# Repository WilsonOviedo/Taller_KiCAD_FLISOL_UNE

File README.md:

# Taller_KiCAD_FLISOL_UNE
Repositorio de taller de KiCAD realizado en el FLISOL 27/04/2019

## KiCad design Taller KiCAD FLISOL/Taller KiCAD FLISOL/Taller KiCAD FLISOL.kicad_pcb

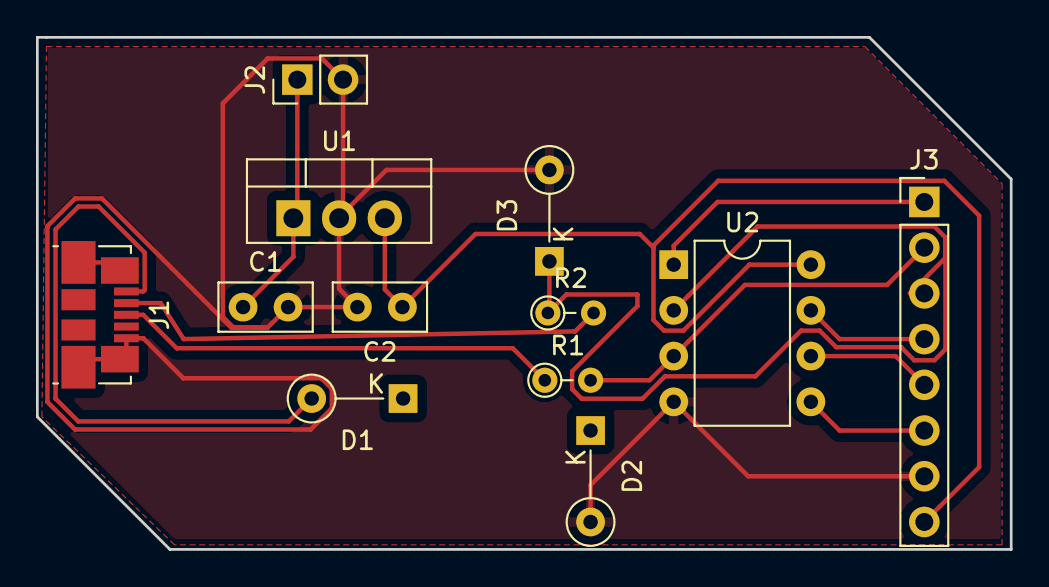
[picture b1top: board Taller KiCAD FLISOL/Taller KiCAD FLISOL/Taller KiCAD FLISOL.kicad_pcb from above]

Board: 2 copper layers, 54.1 x 28.4 mm, 12 parts (0 on the bottom side), 12 nets.

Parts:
C1: 0.33uF; C_Disc_D5.0mm_W2.5mm_P2.50mm
C2: 0.1uF; C_Disc_D5.0mm_W2.5mm_P2.50mm
D1: D; D_DO-35_SOD27_P5.08mm_Vertical_KathodeUp
D2, D3: D_Zener; D_DO-35_SOD27_P5.08mm_Vertical_KathodeUp
J1: USB_B_Micro; USB_Micro-B_Molex_47346-0001
J2: Conn_01x02_Male; PinHeader_1x02_P2.54mm_Vertical
J3: Conn_01x08_Male; PinHeader_1x08_P2.54mm_Vertical
R1, R2: 66.5ohms; R_Axial_DIN0204_L3.6mm_D1.6mm_P2.54mm_Vertical
U1: LM7805_TO220; TO-220-3_Vertical
U2: ATTINY85-20PU; DIP-8_W7.62mm

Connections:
+5V: D1.2, J1.1
/5V_Reg: C2.1, D1.1, J3.8, U1.3, U2.8
D+: D2.1, J3.2, R1.2, U2.3
D-: D3.1, J3.3, R2.1, U2.2
GND: C1.2, C2.2, D2.2, D3.2, J1.5, J2.2, J3.7, U1.2, U2.4
unnamed: C1.1, J2.1, U1.1
unnamed: J1.2, R2.2
unnamed: J1.3, R1.1
unnamed: J3.1, U2.1
unnamed: J3.4, U2.7
unnamed: J3.5, U2.6
unnamed: J3.6, U2.5

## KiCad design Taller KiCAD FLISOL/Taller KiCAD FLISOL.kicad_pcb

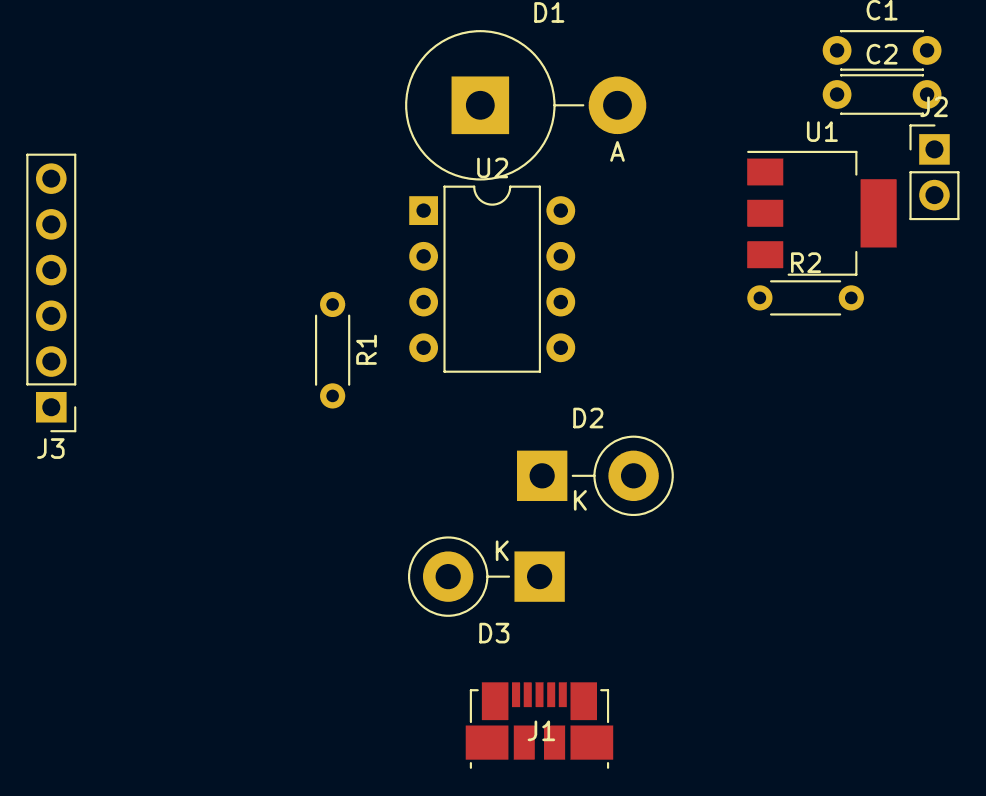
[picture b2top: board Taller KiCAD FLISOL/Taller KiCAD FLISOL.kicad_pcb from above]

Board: 2 copper layers, 12 parts (0 on the bottom side), 12 nets, no tracks yet.

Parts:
C1: 0.22uF; C_Disc_D4.3mm_W1.9mm_P5.00mm
C2: 0.1uF; C_Disc_D4.3mm_W1.9mm_P5.00mm
D1: D; D_5KPW_P7.62mm_Vertical_AnodeUp
D2, D3: D_Zener; D_5W_P5.08mm_Vertical_KathodeUp
J1: USB_B_Micro; USB_Micro-B_Molex_47346-0001
J2: Conn_01x02_Male; PinHeader_1x02_P2.54mm_Vertical
J3: Conn_01x06_Female; PinHeader_1x06_P2.54mm_Vertical
R1, R2: 65.5R; R_Axial_DIN0204_L3.6mm_D1.6mm_P5.08mm_Horizontal
U1: LM7805CT_Obsolete; SOT-223
U2: ATTINY85-20PU; DIP-8_W7.62mm

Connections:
+5V: D1.1, J1.1, U2.8
D+: J3.5, R1.1, U2.3
D-: J3.4, R2.1, U2.2
GND: C1.2, C2.2, D2.2, D3.2, J1.5, J1.6, J2.2, U1.2, U2.4
unnamed: C1.1, J2.1, U1.1
unnamed: D2.1, J1.2, R2.2
unnamed: D3.1, J1.3, R1.2
unnamed: J3.1, U2.5
unnamed: J3.2, U2.6
unnamed: J3.3, U2.7
unnamed: J3.6, U2.1
Vreg: C2.1, D1.2, U1.3

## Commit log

2019-04-26 Create proyect Add attiny85
2019-04-27 Add carpetas y esquema basico
2019-04-27 Placa terminada
2019-04-29 Add presentacion en pdf
